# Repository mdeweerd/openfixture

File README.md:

# OpenFixture

## Goal

The motivation of OpenFixture was to make a parametric fixturing system
that could take fully generated inputs from kicad and produce a test
fixture with minimal effort. The easiest way to use it is through the kicad
python scripting interface.

The project has been extended with Test PCB Schematic generation - you may
want to generate only that without building the proposed fixture.

## Parameters

For most projects (if using the standard BOM) the only parameters you'll
need to set are mat_th and pcb_th. Something like the following should be
sufficient:

```
usage: GenFixture.py [-h] --board BOARD --mat_th MAT_TH --out OUT
                     [--pcb_th PCB_TH] [--pcb_h PCB_H] [--screw_len SCREW_LEN]
                     [--screw_d SCREW_D] [--layer LAYER] [--flayer FLAYER]
                     [--ilayer ILAYER] [--rev REV] [--pogo_d POGO_D]
                     [--washer_th WASHER_TH] [--nut_f2f NUT_F2F]
                     [--nut_c2c NUT_C2C] [--nut_th NUT_TH] [--pivot_d PIVOT_D]
                     [--border BORDER] [--render] [--kicad]
                     [--annular ANNULAR] [--logo LOGO] [--logo-w LOGO_W]
                     [--logo-h LOGO_H] [--pins PINS]
                     [--exclude-size EXCLUDE_SIZE]

optional arguments:
  -h, --help            show this help message and exit
  --board BOARD         <board_name.kicad_pcb>
  --mat_th MAT_TH       material thickness (mm)
  --out OUT             output directory
  --pcb_th PCB_TH       pcb thickness (mm)
  --pcb_h PCB_H         pcb component height (mm)
  --screw_len SCREW_LEN
                        Assembly screw thread length (default = 16mm)
  --screw_d SCREW_D     Assembly screw diameter (default=3mm)
  --layer LAYER         F.Cu | B.Cu
  --flayer FLAYER       Eco1.User | Eco2.User
  --ilayer ILAYER       Eco1.User | Eco2.User
  --rev REV             Override revision
  --pogo_d POGO_D       Pogo hole diameter (default=1.22mm)
  --washer_th WASHER_TH
                        Washer thickness for hinge
  --nut_f2f NUT_F2F     hex nut flat to flat (mm)
  --nut_c2c NUT_C2C     hex nut corner to corner (mm)
  --nut_th NUT_TH       hex nut thickness (mm)
  --pivot_d PIVOT_D     Pivot diameter (mm)
  --border BORDER       Board (ledge) under pcb (mm)
  --render              Generate a 3d render of the final fixture
  --kicad               Generate a KiCad project
  --annular ANNULAR     Annular ring width for PADS on PCB
  --logo LOGO           Override logo
  --logo-w LOGO_W       Set logo width, mm
  --logo-h LOGO_H       Set logo height, mm
  --pins PINS           Extra pins to include (THT/SMD) REF-PINNBR - comma
                        separated
  --exclude-size EXCLUDE_SIZE
                        Module refs to exclude from board size - comma
                        separated
```

The resulting output is:

- A 3D model of the test fixture for visualization (optional, with
  '--render')
- 2D DXF files that can be directly lasercut for assembly (several
  organisations)
- A kicad project for a test board (optional)

## Requirements

- Setup your path to run KiCad's python (or a python with pcbnew).
- You may need to install some modules.\
  Either to your personal directory
  (example for ezdxf module, required for KiCad
  generation):\
  `pip install --user ezdxf`\
  Either
  globally:\
  `pip install ezdxf`

## Recommended workflow for KiCad

1. Clone this repo if you haven't already
2. Setup a project specific bash script (use genfixture.sh as an example),
   and/or add a `fixture.conf` file to your project.
3. Enter board specific info, fixture hardware, material thickness, etc.
4. Whenever the layout changes call ./genfixture.sh (from repo) and pass
   path to .kicad_pcb file.
5. Fixture will be generated in $OUTPUT folder.

## Helper script

`genfixture.sh` is a helper script that you can call with just the path to
the PROJET.kicad_pcb file. You can add more options which will be appended
to the call to `GenFixture.py`.

On windows, that script can be used under cygwin. The `cygwin.setpath`
include script shows how you can set the system paths.

`genfixture.sh` also checks the directory where the project file is located
for a `fixture.conf` configuration file and includes the contents of that
file as a bash include script.

## Hints

- Examine the `genfixture.sh` helper script to learn about option.
- If you want smaller pogo pin holes for the test fixture than the PCB,
  perform multiple generations with different parameters.

## KiCAD Test Schematic & Board Generation

The `generate_kicad.py` script is called from `GenFixture.py` when the
`--kicad` option is added.

This generates a schematic sheet with the test pins connected to global
netnames corresponding to the netnames on the original schematic. It also
generates a board that puts the test pins in the right locations.

You can edit the board to change the EDGES to make a bigger board for
instance. You can edit the schematic to add other connectors for test
purposes or electronics for test purposes.

The best method would be the use of hierarchical sheets so that the POGOPIN
schematic can be regenerated.

## Hardware

- All that is needed is 14xM3 (14mm+) screws, 14xM3 hex nuts, and lasercut
  parts
- Nylon bushings in the main pivot with m3 screws for a smoother joint can
  be used, but this is optional

## Documentation

https://tinylabs.io/openfixture

## BOM

Material needed to build the Fixture: https://tinylabs.io/openfixture-bom

- 15 M3 nuts
- 15 M3 hex nuts
- Pogo sockets
- Pogo pins
- Glue

Pogo pins come in different sizes, and are composed of a socket and a pin.
There are R100 sockets, as well as R50 sockets and other sized. The drill
sizes change accordingly. You can find them from different sources. You can
find several source by looking for `R100-2S` or `R50-2W7`

- DirtyPCBs proposes R100-\* type sockets. Make sure that you use the
  corresponding P100-\* pins
  https://dirtypcbs.com/store/designer/details/ian/12/dirty-pogo-pins
- Aliexpress, Alibaba, Amazon, CDiscount are marketplaces where you can
  find many other vendors.

## STEP export

A standalone scad file is generated.\
Copy the logos and font to the
directory where the generated scad file is located. Or, copy the SCAD file
to the script directory. You can perform
`./convert_shape.py <SCADFILE> out.step` to convert to STEP for instance.

There is a bug in FreeCad 0.19 that prevents generation (on Windows)

## STL export

A standalone scad file is generated.\
Copy the logos and font to the
directory where the generated scad file is located. Or, copy the SCAD file
to the script directory. You can perform
`openscad --render -o out.stl <SCADFILE>` to convert to STL for instance.

## Testpoint validation

To verify that all your testpoints are within the PCB area, you can check
that no checkpoint appears in the `*-validate.dxf` file.

## Assembly

More info including detailed assembly instructions at
https://tinylabs.io/openfixture-assembly

## Dependencies

- Newer version of openscad >= 2015.03-1
- kicad or other EDA software. Please email me if you have instructions for
  other packages so I can add them.

## Known Issues

- When loading the fonts file a new small window opens in Ubuntu. Seems
  innocuous but still annoying \[Only seen on ubuntu 14.04\]
- STEP generation with FreeCAD is not entirely functional

## License

Creative Commons (CC BY-SA 4.0)

## Contributors

- Elliot Buller - Tiny Labs Inc
- Mario DE WEERD - Ynamics

(?) Please email with any pull requests or new feature requests
elliot@tinylabs.io

## Resources

KiCAD PCB generation script initiated from
https://github.com/jaseg/pogojig.git

## Work in progress / possible features

- The generation of a hierchical sheet is work in progress
- 3D models of test sockets and pins are generated. They must be verified
  and could be integrated as KiCad components.
- Mechanical holes should also be "exported" to the KiCad project to allow
  adding guides.
- Add a filter to exclude specific pins.
- KiCad integration (in a distant future)

# Old stuff

## KiCAD export

https://tinylabs.io/openfixture-kicad-export

Getting the test pins from the kicad schematic is integrated in this
project.

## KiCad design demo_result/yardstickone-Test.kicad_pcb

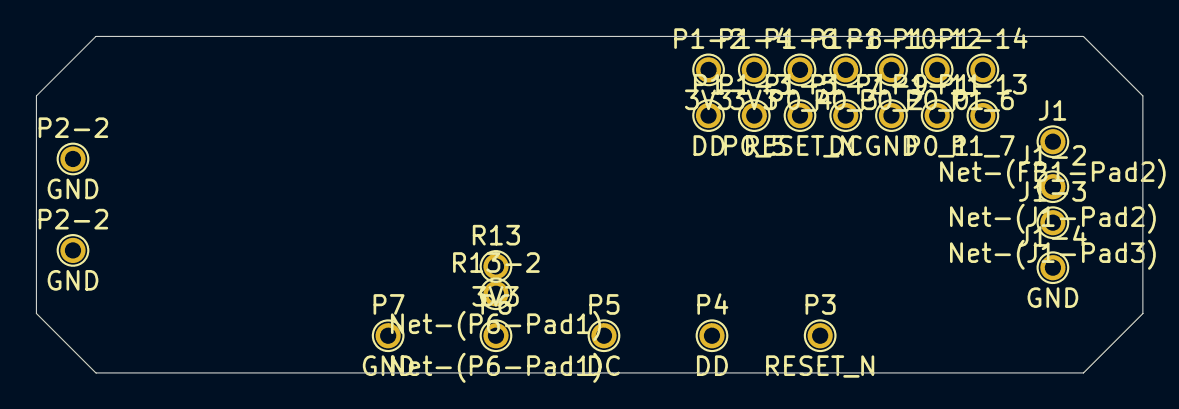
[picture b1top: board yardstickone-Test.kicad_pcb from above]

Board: 2 copper layers, 61.5 x 18.7 mm, 27 parts (0 on the bottom side), 6 nets, no tracks yet.

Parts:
J1: pogo pin 0; None
J1-2: pogo pin 1; None
J1-3: pogo pin 2; None
J1-4: pogo pin 3; None
P1: pogo pin 4; None
P1-2: pogo pin 5; None
P1-3: pogo pin 6; None
P1-4: pogo pin 7; None
P1-5: pogo pin 8; None
P1-6: pogo pin 9; None
P1-7: pogo pin 10; None
P1-8: pogo pin 11; None
P1-9: pogo pin 12; None
P1-10: pogo pin 13; None
P1-11: pogo pin 14; None
P1-12: pogo pin 15; None
P1-13: pogo pin 16; None
P1-14: pogo pin 17; None
P2-2: pogo pin 18; None
P2-2#2: pogo pin 19; None
P3: pogo pin 20; None
P4: pogo pin 21; None
P5: pogo pin 22; None
P6: pogo pin 23; None
P7: pogo pin 24; None
R13: pogo pin 26; None
R13-2: pogo pin 25; None

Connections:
3V3: P1-2.1, P1-4.1, R13.1
DC: P1-7.1, P5.1
DD: P1.1, P4.1
GND: J1-4.1, P1-9.1, P2-2.1, P2-2#2.1, P7.1
unnamed: P6.1, R13-2.1
RESET_N: P1-5.1, P3.1

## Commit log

2017-12-03 added "--render" option, to make 3d render optional
2017-12-03 Made all primitives 2D for peformance gains. Runs in less than 1 second now for a 2D render. 3D render performance is about 250% faster
2017-12-05 beefed up tabs so they don't break so easily
2017-12-12 fixed missing log cabin cut, fixed latch pivot hole being too far back
2017-12-12 scad now uses logo w/h to center
2017-12-12 accepts logo size params
2017-12-12 auto-converts logo from svg to dxf, reads size for use by openscad
2017-12-12 logo now svg format
2017-12-12 ignores logo.dxf
2021-02-02 Add .whitesource configuration file
2021-04-07 WIP for script improvements
2021-04-07 WIP - improved genfixture.sh, added cygwin setup script, need to fix scad script
2021-04-08 Made quoting compatible with windows, not tested on *nix
2021-04-08 Escape backslashes
2021-04-08 Removed printing commands
2021-04-08 Fixed logo option
2021-04-08 Conditional logo dxf generation
2021-04-08 Build mostly functionnal (repaired 3D construction)
2021-04-09 Using 2D model for fixture generation
2021-04-09 Rev0, make RENDER more easily accessible
2021-04-09 Enable component height
2021-04-09 Printing TP information, not rendering 3D from wrapper, removed comment
2021-04-09 Corrected testpoints to test_points
2021-04-09 Generate standalone scad file to allow STEP generation
2021-04-09 Moved execution to later location (after parameter changes)
2021-04-09 Added information about new outputs: scad, validate, and about transformations
2021-04-09 Upgraded Freecad version
2021-04-11 Allow user to specify pins (such as THT)
2021-04-11 WIP for better edge extraction
2021-04-11 2nd logo import improved, fix issues related to PCB targets messing up size
2021-04-11 Suppressed message showing freecad path
2021-04-11 Improved PCB outline management, option for pogo diameter, SVG for fixture, alternative layout
2021-04-11 Removed leftover from verification of 3DMODEL
2021-04-11 Read ficture.conf from project file directory
2021-04-11 Enable max_height_component
2021-04-11 Fixture v2 DXF generation offset correction, LAYER variable correction en genfixture, CLI quote correction
2021-04-11 logo size & position corrected
2021-04-11 Ignore user logo
2021-04-13 Quote path to kicad python to cope with spaces.
2021-04-13 Add initial small library of test pin
2021-04-14 Prepared adding 3D modeld
2021-04-17 Add openscad model and pogopin model generation
2021-04-17 Added more pogo pin models
2021-04-17 Updated information about models
2021-04-17 Added R50 & improved step comments
2021-04-18 More information in the files, correction to license label, improved shell script
2021-04-18 Converted generate_kicad.py to python 2.7 compatibility and not reading from svg
2021-04-18 Netnames can be specified and are added to the schematic and pcb
2021-04-18 Complete kicad test pcb generation, annular ring, global labels, ...
2021-04-19 Added doDemo.sh demo script, documentation updates, added demo result
2021-04-19 Added information about some requirements
2021-05-19 Updated steps after measuring R50-2W7 sockets and P50 pins
2021-05-19 Optimisation for object loop
2021-06-13 Add files via upload
    Add script to run it under Windows enviroment
2021-09-16 Add bat file to launch demo from Windows
2021-11-24 Regenerated pins with color
2024-01-05 Add pre-commit flow & related adjustments
